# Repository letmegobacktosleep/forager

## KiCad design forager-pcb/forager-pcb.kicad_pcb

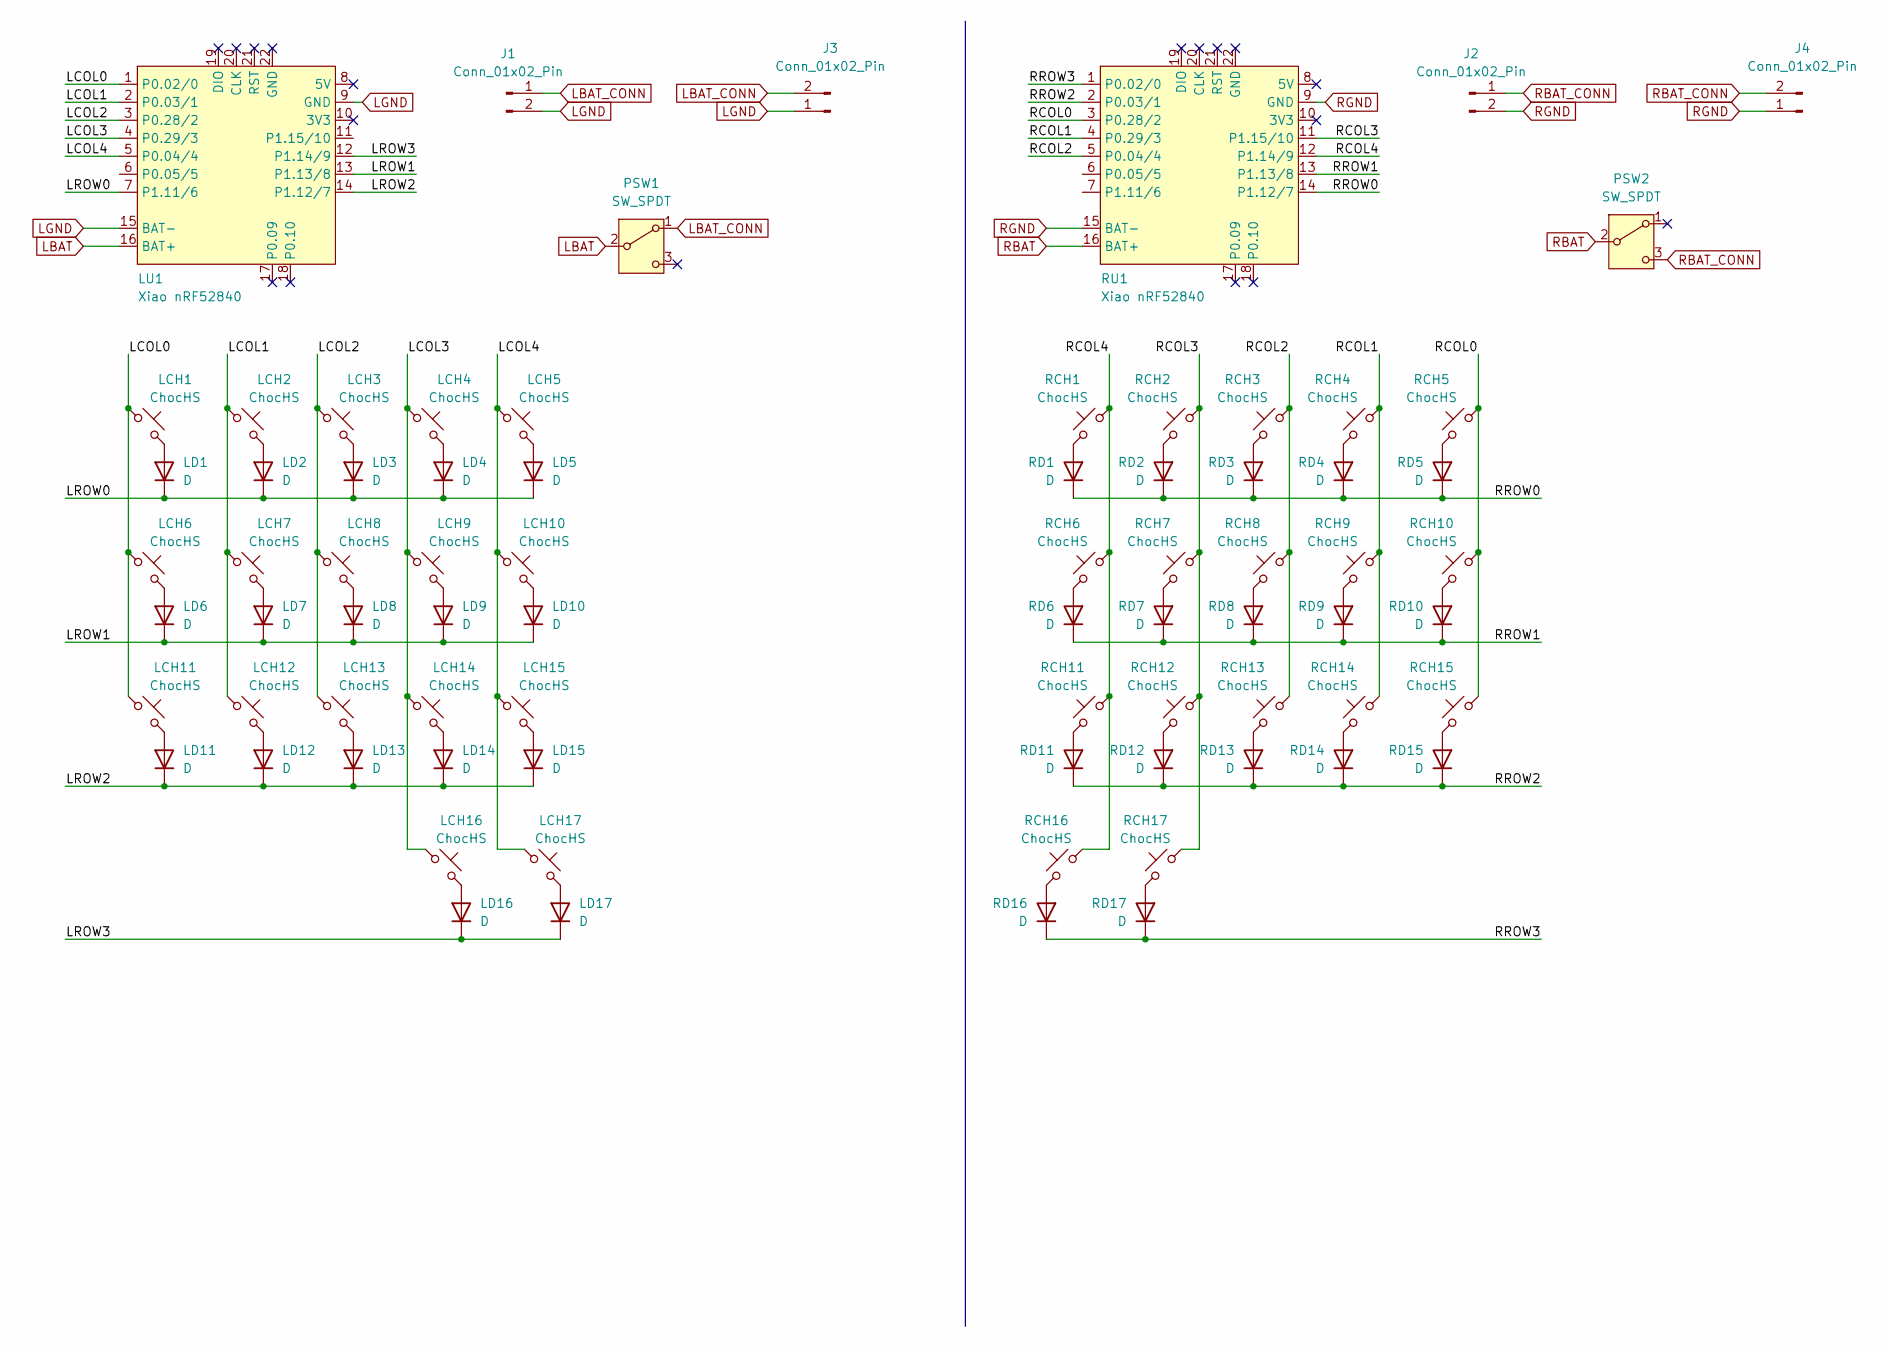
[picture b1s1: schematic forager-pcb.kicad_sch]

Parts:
J1, J2: Conn_01x02_Pin; JST_ACH_BM02B-ACHSS-GAN-ETF_1x02-1MP_P1.20mm_Vertical; LCSC C5118738
J3, J4: Conn_01x02_Pin; PinHeader_1x02_P2.54mm_Vertical; LCSC N/A
LCH1, LCH2, LCH3, LCH4, LCH5, LCH6, LCH7, LCH8, LCH9, LCH10, LCH11, LCH12, LCH13, LCH14, LCH15, LCH16, LCH17: ChocHS; SW_choc_v1_HS_MBK; LCSC C5333465
LD1, LD2, LD3, LD4, LD5, LD6, LD7, LD8, LD9, LD10, LD11, LD12, LD13, LD14, LD15, LD16, LD17: D; D_SOD-123; LCSC C81598
LU1: Xiao nRF52840; xiao-ble-smd-cutout; LCSC N/A
PSW1, PSW2: SW_SPDT; SW_MSK12C02-HB; LCSC C431540
RCH1, RCH2, RCH3, RCH4, RCH5, RCH6, RCH7, RCH8, RCH9, RCH10, RCH11, RCH12, RCH13, RCH14, RCH15, RCH16, RCH17: ChocHS; SW_choc_v1_HS_MBK; LCSC C5333465
RD1, RD2, RD3, RD4, RD5, RD6, RD7, RD8, RD9, RD10, RD11, RD12, RD13, RD14, RD15, RD16, RD17: D; D_SOD-123; LCSC C81598
RU1: Xiao nRF52840; xiao-ble-smd-cutout; LCSC N/A

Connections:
/LCOL0: LCH1.1, LCH6.1, LCH11.1, LU1.1 (P0.02/0)
/LCOL1: LCH2.1, LCH7.1, LCH12.1, LU1.2 (P0.03/1)
/LCOL2: LCH3.1, LCH8.1, LCH13.1, LU1.3 (P0.28/2)
/LCOL3: LCH4.1, LCH9.1, LCH14.1, LCH16.1, LU1.4 (P0.29/3)
/LCOL4: LCH5.1, LCH10.1, LCH15.1, LCH17.1, LU1.5 (P0.04/4)
/LROW0: LD1.1 (K), LD2.1 (K), LD3.1 (K), LD4.1 (K), LD5.1 (K), LU1.7 (P1.11/6)
/LROW1: LD6.1 (K), LD7.1 (K), LD8.1 (K), LD9.1 (K), LD10.1 (K), LU1.13 (P1.13/8)
/LROW2: LD11.1 (K), LD12.1 (K), LD13.1 (K), LD14.1 (K), LD15.1 (K), LU1.14 (P1.12/7)
/LROW3: LD16.1 (K), LD17.1 (K), LU1.12 (P1.14/9)
/RCOL0: RCH5.1, RCH10.1, RCH15.1, RU1.3 (P0.28/2)
/RCOL1: RCH4.1, RCH9.1, RCH14.1, RU1.4 (P0.29/3)
/RCOL2: RCH3.1, RCH8.1, RCH13.1, RU1.5 (P0.04/4)
/RCOL3: RCH2.1, RCH7.1, RCH12.1, RCH17.1, RU1.11 (P1.15/10)
/RCOL4: RCH1.1, RCH6.1, RCH11.1, RCH16.1, RU1.12 (P1.14/9)
/RROW0: RD1.1 (K), RD2.1 (K), RD3.1 (K), RD4.1 (K), RD5.1 (K), RU1.14 (P1.12/7)
/RROW1: RD6.1 (K), RD7.1 (K), RD8.1 (K), RD9.1 (K), RD10.1 (K), RU1.13 (P1.13/8)
/RROW2: RD11.1 (K), RD12.1 (K), RD13.1 (K), RD14.1 (K), RD15.1 (K), RU1.2 (P0.03/1)
/RROW3: RD16.1 (K), RD17.1 (K), RU1.1 (P0.02/0)
LBAT: LU1.16 (BAT+), PSW1.2 (B)
LBAT_CONN: J1.1, J3.2, PSW1.1 (A)
LGND: J1.2, J3.1, LU1.9 (GND), LU1.15 (BAT-)
unnamed: LCH1.2, LD1.2 (A)
unnamed: LCH2.2, LD2.2 (A)
unnamed: LCH3.2, LD3.2 (A)
unnamed: LCH4.2, LD4.2 (A)
unnamed: LCH5.2, LD5.2 (A)
unnamed: LCH6.2, LD6.2 (A)
unnamed: LCH7.2, LD7.2 (A)
unnamed: LCH8.2, LD8.2 (A)
unnamed: LCH9.2, LD9.2 (A)
unnamed: LCH10.2, LD10.2 (A)
unnamed: LCH11.2, LD11.2 (A)
unnamed: LCH12.2, LD12.2 (A)
unnamed: LCH13.2, LD13.2 (A)
unnamed: LCH14.2, LD14.2 (A)
unnamed: LCH15.2, LD15.2 (A)
unnamed: LCH16.2, LD16.2 (A)
unnamed: LCH17.2, LD17.2 (A)
unnamed: RCH1.2, RD1.2 (A)
unnamed: RCH2.2, RD2.2 (A)
unnamed: RCH3.2, RD3.2 (A)
unnamed: RCH4.2, RD4.2 (A)
unnamed: RCH5.2, RD5.2 (A)
unnamed: RCH6.2, RD6.2 (A)
unnamed: RCH7.2, RD7.2 (A)
unnamed: RCH8.2, RD8.2 (A)
unnamed: RCH9.2, RD9.2 (A)
unnamed: RCH10.2, RD10.2 (A)
unnamed: RCH11.2, RD11.2 (A)
unnamed: RCH12.2, RD12.2 (A)
unnamed: RCH13.2, RD13.2 (A)
unnamed: RCH14.2, RD14.2 (A)
unnamed: RCH15.2, RD15.2 (A)
unnamed: RCH16.2, RD16.2 (A)
unnamed: RCH17.2, RD17.2 (A)
RBAT: PSW2.2 (B), RU1.16 (BAT+)
RBAT_CONN: J2.1, J4.2, PSW2.3 (C)
RGND: J2.2, J4.1, RU1.9 (GND), RU1.15 (BAT-)

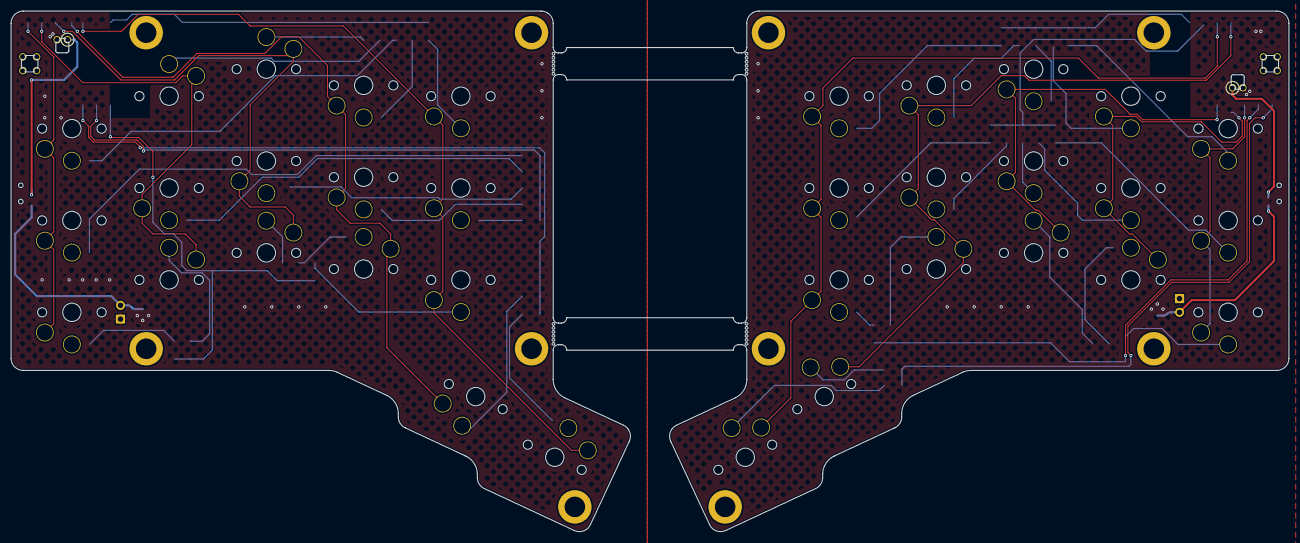
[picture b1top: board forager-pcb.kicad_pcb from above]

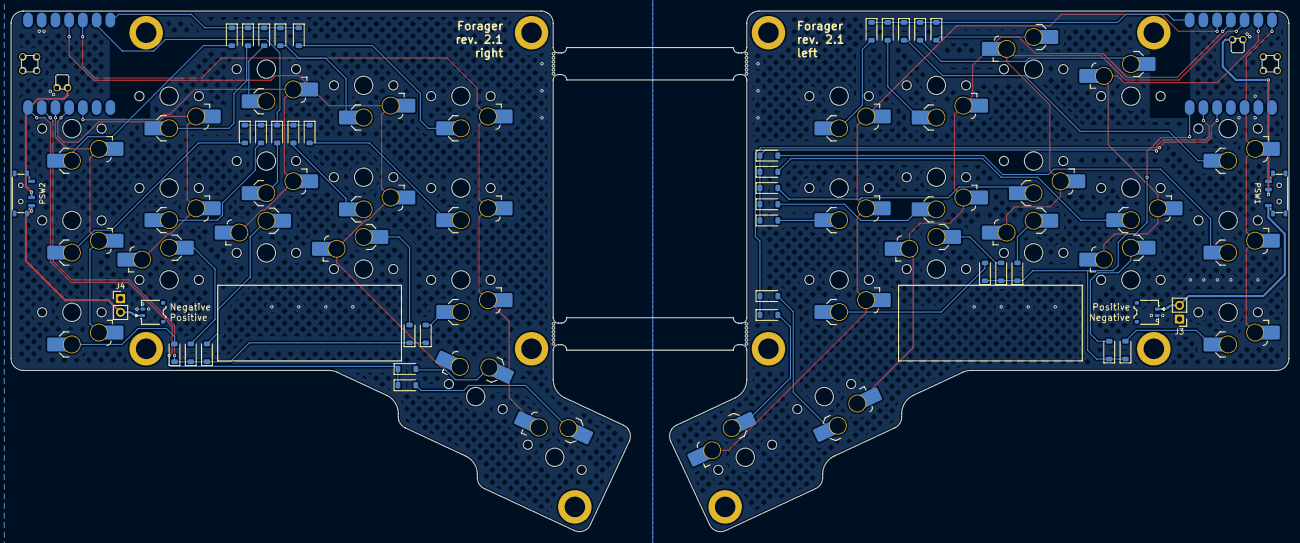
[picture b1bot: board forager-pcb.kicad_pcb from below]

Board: 2 copper layers, 236.5 x 96.3 mm, 76 parts (76 on the bottom side), 58 nets.

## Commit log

2025-09-10 add a power switch, change the battery test points to through hole
